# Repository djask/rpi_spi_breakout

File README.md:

# rpi_spi-breakout

 A simple Raspberry Pi breakout hat to make in circuit programming and chip programming easier. Takes a standard SOP16 ZIF socket so should be compatible with all the aliexpress chip adapters as well.

 Has UART, I2C, SPI breakouts for most common chips.

 Also has a header for a TTL-232R-3V3 UART adapter (5v not connected)

 ## BOM
 - 1x PCB
 - 22x Standard Header Pins Pins
 - 2x Jumpers for Write Protect and Hold
 - 1x ZIF socket

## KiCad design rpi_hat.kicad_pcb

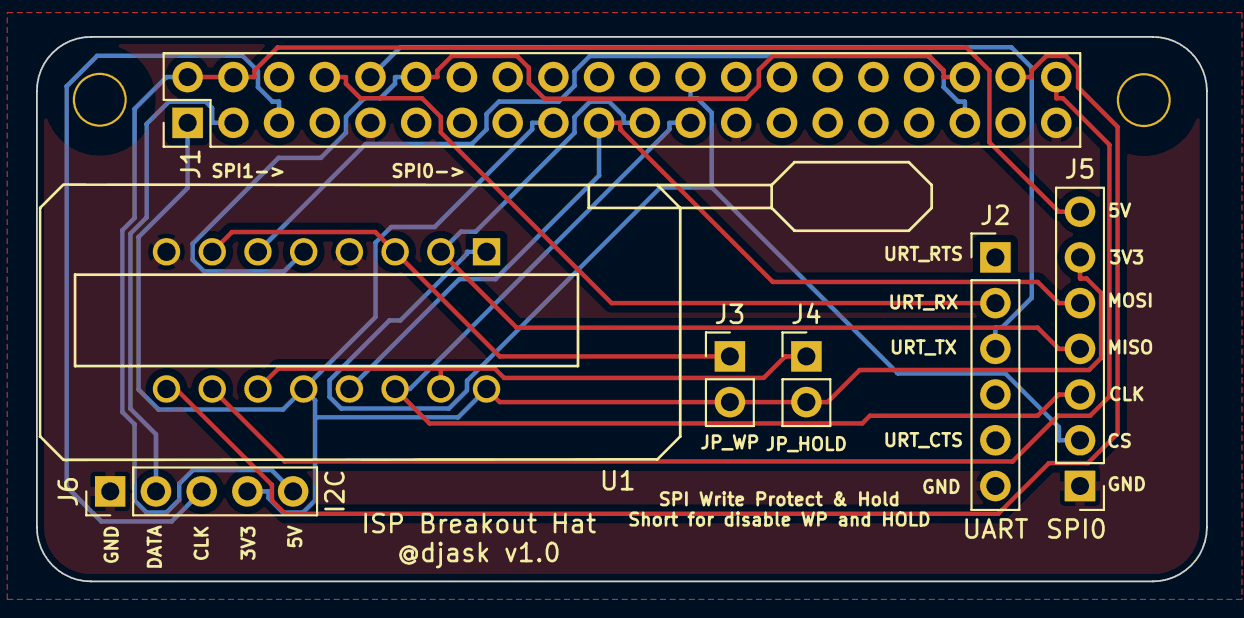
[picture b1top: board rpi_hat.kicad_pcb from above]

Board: 2 copper layers, 65.0 x 30.2 mm, 9 parts (0 on the bottom side), 17 nets.

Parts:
H1, H2: 3mm_Mounting_Hole; NPTH_3mm_ID
J1: GPIO; PinHeader_2x20_P2.54mm_Vertical
J2: UART; PinHeader_1x06_P2.54mm_Vertical
J3: JP_WP; PinHeader_1x02_P2.54mm_Vertical
J4: JP_HOLD; PinHeader_1x02_P2.54mm_Vertical
J5: SPI0; PinHeader_1x07_P2.54mm_Vertical
J6: I2C; PinHeader_1x05_P2.54mm_Vertical
U1: 216-3340

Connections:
+3V3: J1.1, J1.17, J3.2, J4.2, J5.6, J6.4, U1.12, U1.16
+5V: J1.2, J1.4, J5.7, J6.5
GND: J1.6, J1.9, J1.14, J1.20, J1.25, J1.30, J1.34, J1.39, J2.6, J5.1, J6.1, U1.4, U1.8
I2C_CLK: J1.5, J6.3
I2C_DATA: J1.3, J6.2
SPI0_CLK: J1.23, J5.3, U1.14
SPI0_CS: J1.24, J5.2, U1.1
SPI0_MISO: J1.21, J5.4, U1.2
SPI0_MOSI: J1.19, J5.5, U1.13
SPI1_CLK: J1.40, U1.10
SPI1_CS: J1.12, J1.36, U1.5
SPI1_MISO: J1.35, U1.6
SPI1_MOSI: J1.38, U1.9
SPI_HOLD: J4.1, U1.11, U1.15
SPI_WP: J3.1, U1.3, U1.7
UART_RX: J1.8, J2.2
UART_TX: J1.10, J2.3

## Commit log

2022-09-03 First and probably final working version
